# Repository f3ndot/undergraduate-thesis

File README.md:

My 2013/2014 undergraduate thesis for Computer Science at Ryerson University

### [Thesis Proposal](http://www.justinbull.ca/thesis/proposal.pdf) ###

### Copyright & License ###

- The source code for the web app and Arduino sketches fall under the MIT licence.
- The thesis documents, and all related academic works, are licensed under the Creative Commons [Attribution-ShareAlike 4.0 International](http://creativecommons.org/licenses/by-sa/4.0/) license. The attribution name should be Justin A. S. Bull linked to `http://www.justinbull.ca`

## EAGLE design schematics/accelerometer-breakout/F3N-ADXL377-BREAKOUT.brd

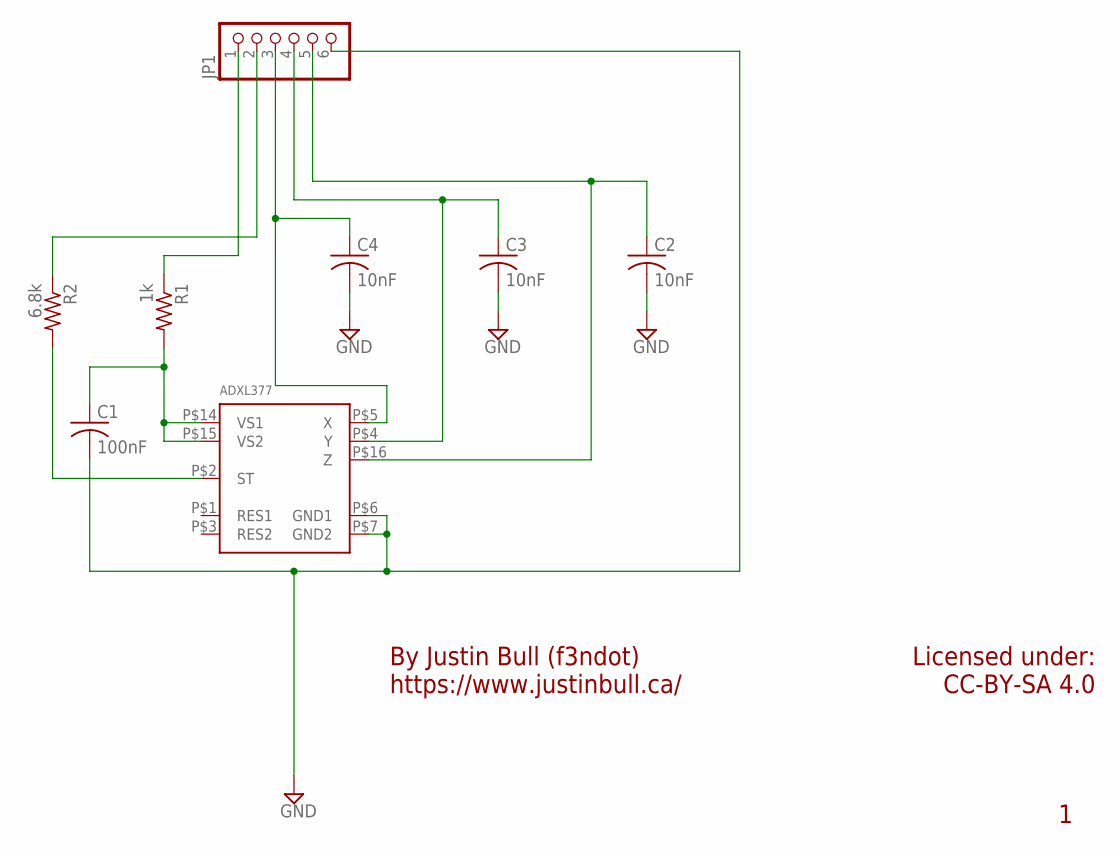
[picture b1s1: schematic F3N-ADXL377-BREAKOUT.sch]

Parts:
ADXL377: ACCEL_ADXL377LFCSP_LQ; LFCSP_LQ_CP-16-28
C1: 100nF; C050-030X075
C2, C3, C4: 10nF; C050-030X075
JP1: PINHD-1X6; 1X06
R1: 1k; 0204/7
R2: 6.8k; 0204/7

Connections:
GND: ADXL377.P$6 (GND1), ADXL377.P$7 (GND2), C1.2, C2.2, C3.2, C4.2, JP1.6
unnamed: ADXL377.P$14 (VS1), ADXL377.P$15 (VS2), C1.1, R1.2
unnamed: ADXL377.P$2 (ST), R2.2
ST: JP1.2, R2.1
VS: JP1.1, R1.1
X: ADXL377.P$5 (X), C4.1, JP1.3
Y: ADXL377.P$4 (Y), C3.1, JP1.4
Z: ADXL377.P$16 (Z), C2.1, JP1.5

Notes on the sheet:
Licensed under: CC-BY-SA 4.0
By Justin Bull (f3ndot) https://www.justinbull.ca/

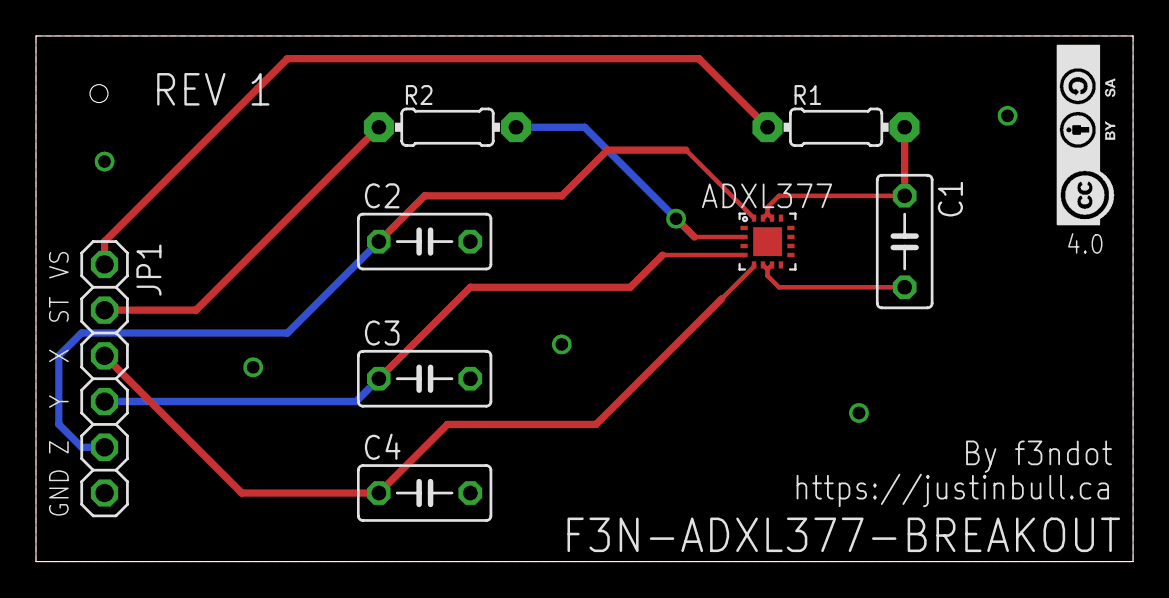
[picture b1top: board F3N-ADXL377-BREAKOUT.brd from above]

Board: 2 copper layers, 60.9 x 29.2 mm, 8 parts (0 on the bottom side), 8 nets.

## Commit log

2013-10-30 Make a crappy working title for the proposal
2013-10-30 Add newline to EOF
2013-10-30 Make document thesis format, explicitly delcare UTF-8 formatting
2013-10-30 Rough outline considerations for proposal
    Go back to report documentclass and format my authorship a bit better too
2013-10-30 Remove BS, add lipsum, add email
2013-11-02 Describe the problem, web app, and device in decent detail
2013-11-02 Mention 140 bytes in paranthesis
2013-11-02 Draft prototype section
2013-11-02 Add generated PDF for v1.0
2013-11-02 Add a summarizing paragraph in Cyclist Problem and rearrange starting sentence in A Tangible Solution
2013-11-02 Add a footnote explaining monthly service fee
2013-11-02 Remove superfluous article
2013-11-02 Rephrased final sentence of The Device paragraph
2013-11-02 Mention device guesses collision type in API call
2013-11-02 Remove superfluous "the"
2013-11-02 Remove paranthesis
2013-11-03 Add background reading and research sections & more;
    The proposal is slightly modified to conform with the CMF:
    - scope of background reading to be carried out
    - research work to be carried out
    - expected results of the research
2013-11-03 Proof reading
2013-11-03 Use microtype and todonotes packages
2013-11-03 TODO for mentioning bulk SIM subscription
2013-11-06 Move proposal files into documents dir
2013-11-06 Add CC BY-SA 3.0 license to all documents in repo;
    Also mentions MIT license will be used for the code.
2013-11-06 Add Creative Commons copyright
2013-11-06 Remove unneeded todo notes
2013-11-06 Make CC license text BY-SA as well, format it a bit
2013-11-07 Create an empty Rails 4.0.1 project
2013-11-07 Generate Page scaffold and use bootstrap
2013-11-07 Make welcome page with scribd embed
2013-11-07 Add image logo resources
2013-11-07 Use logo resource
2013-11-07 Add CC BY-SA 3.0 LICENSE to resources
2013-11-07 Link to proposal
2013-11-07 Add README to rails app
2013-11-07 Attempt to use relative path for logo
2013-11-07 Format headings in Rails README
2013-12-10 Install Twilio and Grape gems
2013-12-15 Patch to 4.0.2
2013-12-15 Add logo stuf
2013-12-15 Set up better dev environment
2013-12-15 Use thin
2013-12-15 Generate scaffold for Device, LogEntry, and AccelerometerDatum
2013-12-15 Remove scaffold CSS and build .active nav link helper
2013-12-15 Add simple_form with bootstrap generation
2013-12-15 Make a license page in webapp, update CC license to 4.0
2013-12-15 Clarify preference copy
2013-12-15 Clarify URL preference too
2013-12-16 Remove webapp from this repo
2013-12-16 Add webapp into repo from a submodule.
2013-12-23 Ignore EAGLE stuff
2013-12-23 Import half-finished F3N-ADXL377-BREAKOUT;
    Two things need to happen:
    - Change the x, y, z capacitors to be be in parallel to ground instead of series to JP1
    - Redesign the board to be an Arduino shield
2013-12-23 Routed, t/b GND plane, Cap parallel fix
2013-12-23 Change CC-BY-SA to CC BY-SA
